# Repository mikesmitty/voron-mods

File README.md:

View this project on [CADLAB.io](https://cadlab.io/project/28137). 

# voron-mods

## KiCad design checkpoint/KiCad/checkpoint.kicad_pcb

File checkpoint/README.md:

# Checkpoint CANBUS board
STM32 CAN bus board for Klipper, modeled to fit over the A stepper on a Voron 2.4R2

# Development
View this project on [CADLAB.io](https://cadlab.io/project/28137/main/files/checkpoint/KiCad).

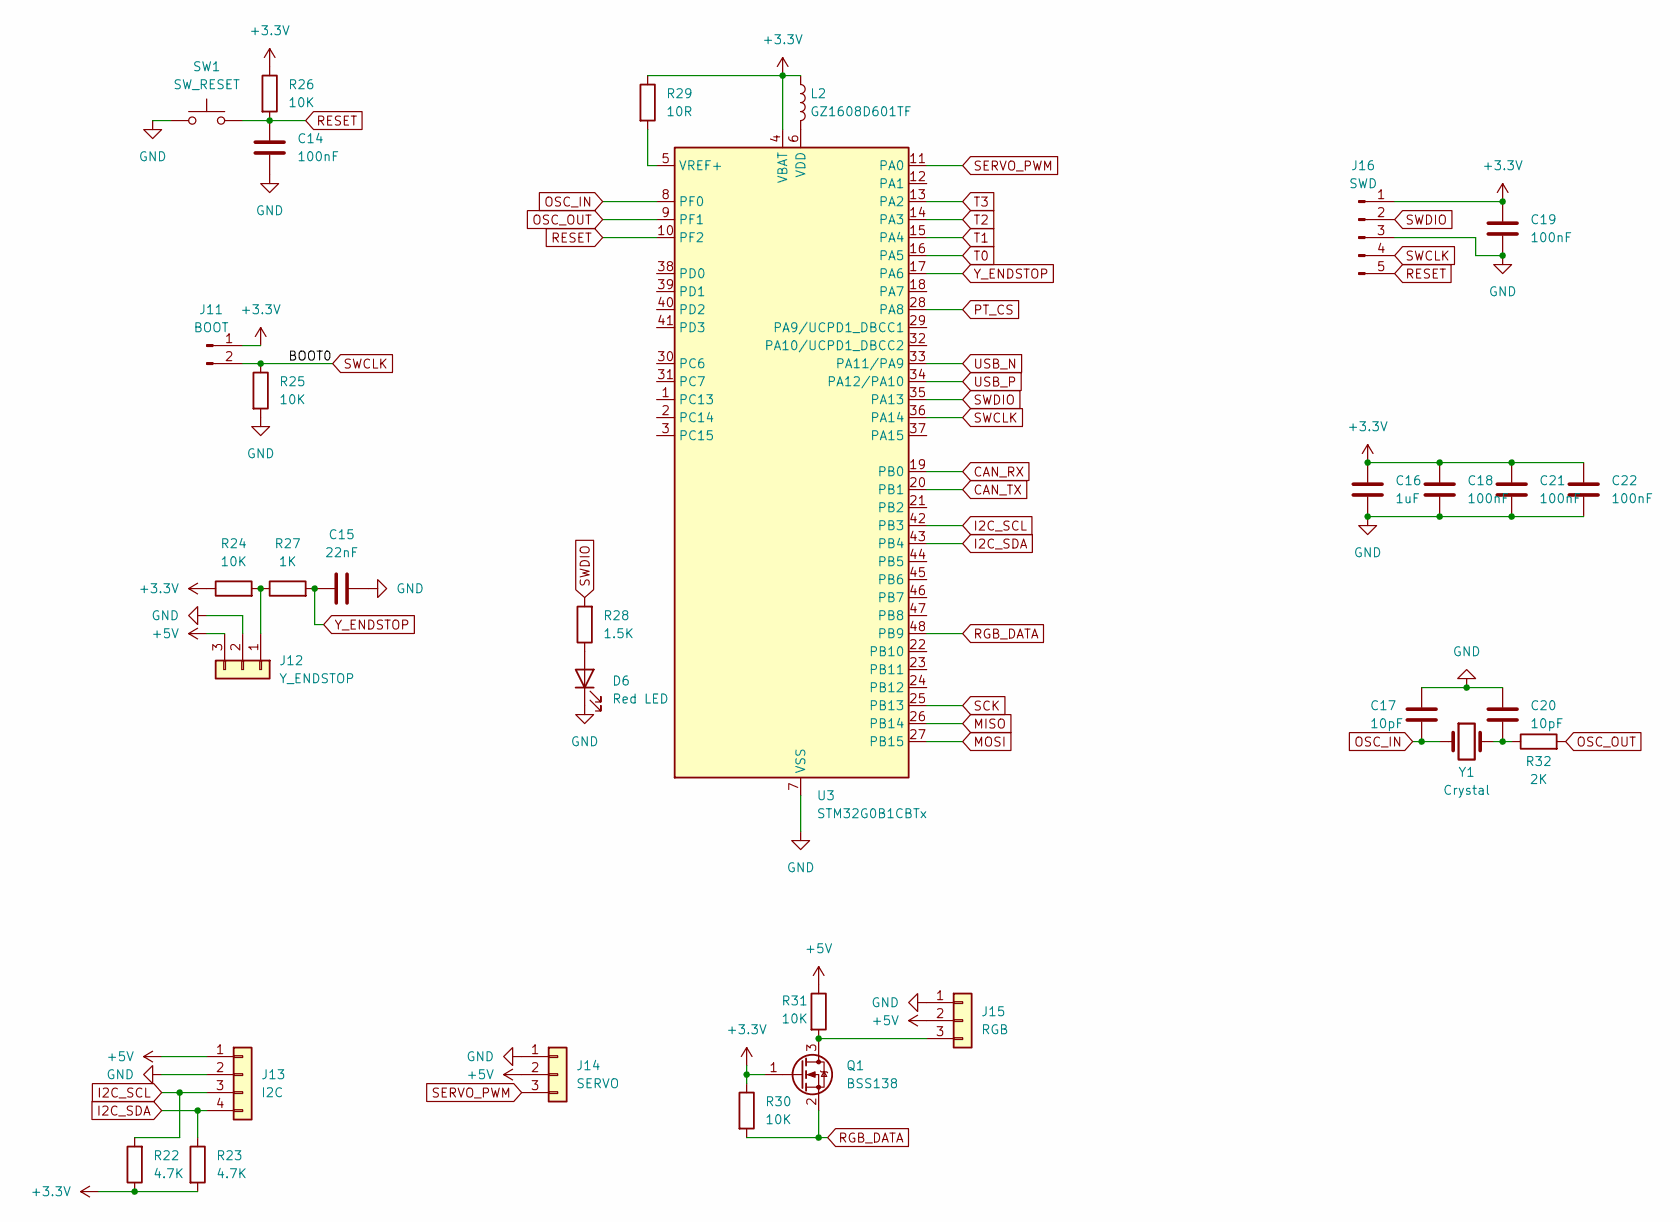
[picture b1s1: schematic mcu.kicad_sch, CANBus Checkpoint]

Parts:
C14, C18, C19, C21, C22: 100nF; C_0402_1005Metric
C15: 22nF; C_0603_1608Metric
C16: 1uF; C_0603_1608Metric
C17, C20: 10pF; C_0603_1608Metric
D6: Red LED; LED_0805_2012Metric
J11: BOOT; PinHeader_1x02_P2.54mm_Vertical
J12: Y_ENDSTOP; JST_XH_S3B-XH-A_1x03_P2.50mm_Horizontal
J13: I2C; JST_XH_B4B-XH-A_1x04_P2.50mm_Vertical
J14: SERVO; JST_XH_B3B-XH-A_1x03_P2.50mm_Vertical
J15: RGB; JST_XH_B3B-XH-A_1x03_P2.50mm_Vertical
J16: SWD; PinHeader_1x05_P2.54mm_Vertical
L2: GZ1608D601TF; L_0603_1608Metric
Q1: BSS138; SOT-23
R22, R23: 4.7K; R_0603_1608Metric
R24, R25, R26, R30, R31: 10K; R_0603_1608Metric
R27: 1K; R_0603_1608Metric
R28: 1.5K; R_0603_1608Metric
R29: 10R; R_0603_1608Metric
R32: 2K; R_0603_1608Metric
SW1: SW_RESET; SW_Push_1P1T_XKB_TS-1187A
U3: STM32G0B1CBTx; LQFP-48_7x7mm_P0.5mm
Y1: Crystal; Crystal_SMD_5032-2Pin_5.0x3.2mm

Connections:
+3.3V: C16.1, C18.1, C19.1, C21.1, C22.1, J11.1, J16.1, L2.1, Q1.1 (G), R22.1, R23.2, R24.1, R26.1, R29.1, R30.1, U3.4 (VBAT); also elsewhere on the board
+5V: J12.3, J13.1, J14.2, J15.2, R31.1; also elsewhere on the board
CAN_RX: U3.19 (PB0); also elsewhere on the board
CAN_TX: U3.20 (PB1); also elsewhere on the board
GND: C14.2, C15.2, C16.2, C17.2, C18.2, C19.2, C20.1, C21.2, C22.2, D6.1 (K), J12.2, J13.2, J14.1, J15.1, J16.3, R25.2, SW1.1, U3.7 (VSS); also elsewhere on the board
I2C_SCL: J13.3, R22.2, U3.42 (PB3)
I2C_SDA: J13.4, R23.1, U3.43 (PB4)
MISO: U3.26 (PB14); also elsewhere on the board
MOSI: U3.27 (PB15); also elsewhere on the board
unnamed: C20.2, R32.1, Y1.2
unnamed: D6.2 (A), R28.1
unnamed: J12.1, R24.2, R27.1
unnamed: J15.3, Q1.3 (D), R31.2
unnamed: L2.2, U3.6 (VDD)
unnamed: R29.2, U3.5 (VREF+)
OSC_IN: C17.1, U3.8 (PF0), Y1.1
OSC_OUT: R32.2, U3.9 (PF1)
PT_CS: U3.28 (PA8); also elsewhere on the board
RESET: C14.1, J16.5, R26.2, SW1.2, U3.10 (PF2)
RGB_DATA: Q1.2 (S), R30.2, U3.48 (PB9)
SCK: U3.25 (PB13); also elsewhere on the board
SERVO_PWM: J14.3, U3.11 (PA0)
SWCLK: J11.2, J16.4, R25.1, U3.36 (PA14)
SWDIO: J16.2, R28.2, U3.35 (PA13)
T0: U3.16 (PA5); also elsewhere on the board
T1: U3.15 (PA4); also elsewhere on the board
T2: U3.14 (PA3); also elsewhere on the board
T3: U3.13 (PA2); also elsewhere on the board
USB_N: U3.33 (PA11/PA9); also elsewhere on the board
USB_P: U3.34 (PA12/PA10); also elsewhere on the board
Y_ENDSTOP: C15.1, R27.2, U3.17 (PA6)

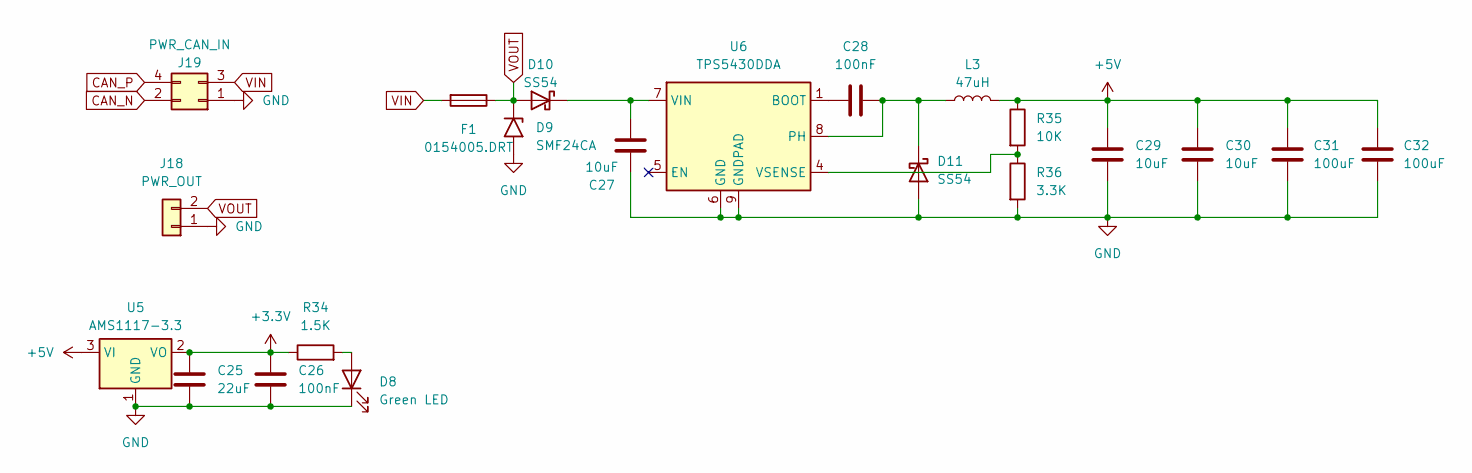
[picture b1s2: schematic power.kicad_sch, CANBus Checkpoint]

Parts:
C25: 22uF; C_0805_2012Metric
C26, C28: 100nF; C_0402_1005Metric
C27, C29, C30: 10uF; C_0805_2012Metric
C31, C32: 100uF; C_1206_3216Metric
D8: Green LED; LED_0805_2012Metric
D9: SMF24CA; D_SOD-123F
D10, D11: SS54; D_SMA
F1: 0154005.DRT; Fuseholder_Littelfuse_Nano2_154x
J18: PWR_OUT; TerminalBlock_Phoenix_MKDS-1,5-2-5.08_1x02_P5.08mm_Horizont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
J19: PWR_CAN_IN; Molex_Micro-Fit_3.0_43045-0412_2x02_P3.00mm_Vertical
L3: 47uH; L_Bourns_SRP7050WA_7.9x7.3mm
R34: 1.5K; R_0603_1608Metric
R35: 10K; R_0603_1608Metric
R36: 3.3K; R_0603_1608Metric
U5: AMS1117-3.3; SOT-223-3_TabPin2
U6: TPS5430DDA; TI_SO-PowerPAD-8_ThermalVias

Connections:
+3.3V: C25.1, C26.1, R34.1, U5.2 (VO); also elsewhere on the board
+5V: C29.1, C30.1, C31.1, C32.1, L3.2, R35.1, U5.3 (VI); also elsewhere on the board
CAN_N: J19.2; also elsewhere on the board
CAN_P: J19.4; also elsewhere on the board
GND: C25.2, C26.2, C27.2, C29.2, C30.2, C31.2, C32.2, D8.1 (K), D9.2 (A2), D11.2 (A), J18.1, J19.1, R36.2, U5.1 (GND), U6.6 (GND), U6.9 (GNDPAD); also elsewhere on the board
unnamed: D8.2 (A), R34.2
unnamed: C27.1, D10.1 (K), U6.7 (VIN)
unnamed: C28.2, D11.1 (K), L3.1, U6.8 (PH)
unnamed: C28.1, U6.1 (BOOT)
unnamed: R35.2, R36.1, U6.4 (VSENSE)
VIN: F1.2, J19.3
VOUT: D9.1 (A1), D10.2 (A), F1.1, J18.2

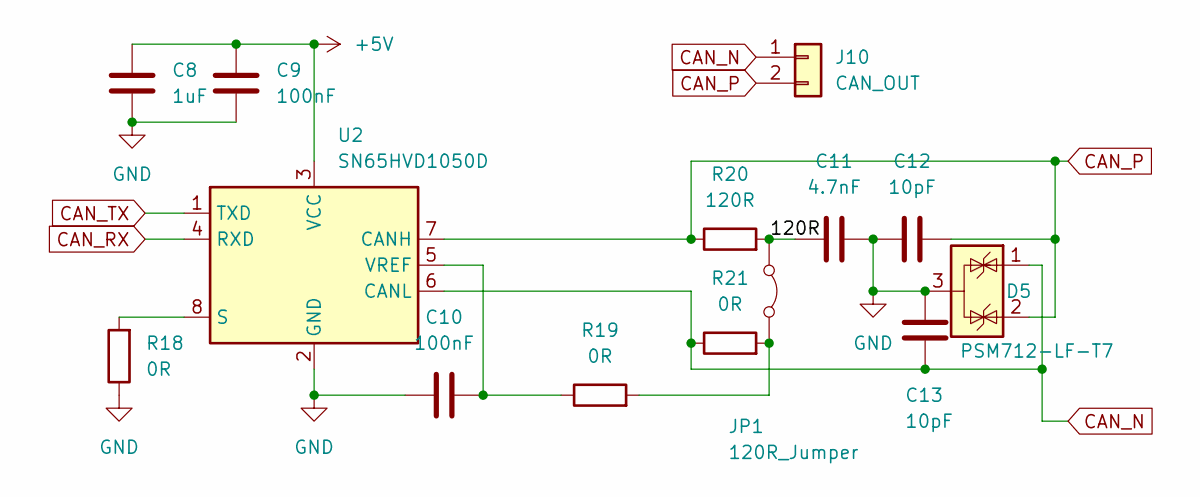
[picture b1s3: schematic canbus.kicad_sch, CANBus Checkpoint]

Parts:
C8: 1uF; C_0603_1608Metric
C9, C10: 100nF; C_0402_1005Metric
C11: 4.7nF; C_0603_1608Metric
C12, C13: 10pF; C_0603_1608Metric
D5: PSM712-LF-T7; SOT-23
J10: CAN_OUT; JST_XH_B2B-XH-A_1x02_P2.50mm_Vertical
JP1: 120R_Jumper; PinHeader_1x02_P2.54mm_Vertical
R18, R19, R21: 0R; R_0603_1608Metric
R20: 120R; R_0603_1608Metric
U2: SN65HVD1050D; SOIC-8_3.9x4.9mm_P1.27mm

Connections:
+5V: C8.2, C9.2, U2.3 (VCC); also elsewhere on the board
/CANBUS/120R: C11.1, JP1.1 (A), R20.2
CAN_N: C13.1, D5.1 (K), J10.1, R21.1, U2.6 (CANL); also elsewhere on the board
CAN_P: C12.2, D5.2 (K), J10.2, R20.1, U2.7 (CANH); also elsewhere on the board
CAN_RX: U2.4 (RXD); also elsewhere on the board
CAN_TX: U2.1 (TXD); also elsewhere on the board
GND: C8.1, C9.1, C10.1, C11.2, C12.1, C13.2, D5.3 (A), R18.1, U2.2 (GND); also elsewhere on the board
unnamed: JP1.2 (B), R19.2, R21.2
unnamed: R18.2, U2.8 (S)
unnamed: C10.2, R19.1, U2.5 (VREF)

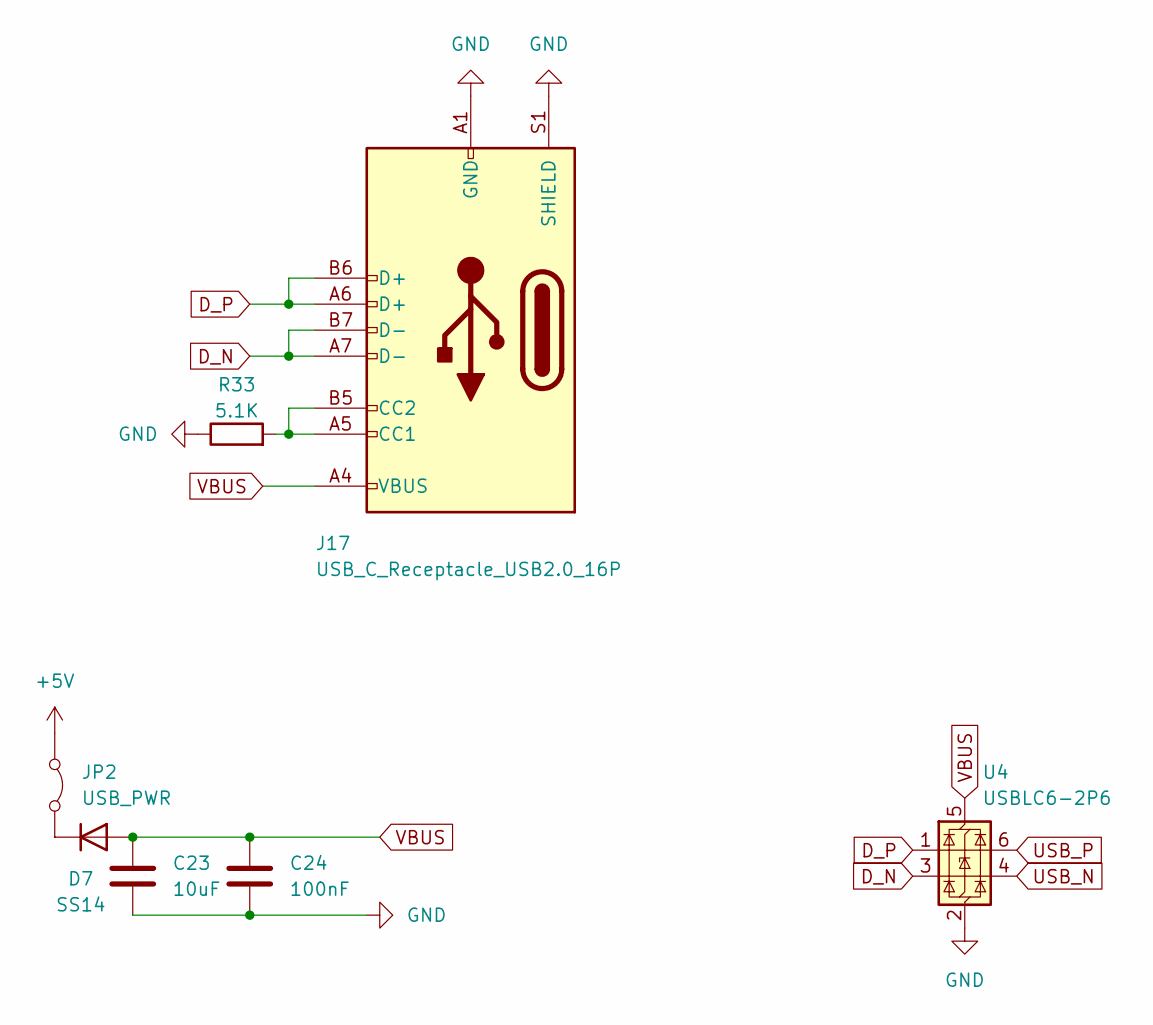
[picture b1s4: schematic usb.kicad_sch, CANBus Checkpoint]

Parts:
C23: 10uF; C_0805_2012Metric
C24: 100nF; C_0402_1005Metric
D7: SS14; D_SMA
J17: USB_C_Receptacle_USB2.0_16P; USB_C_14P_VERT_XUNPU
JP2: USB_PWR; PinHeader_1x02_P2.54mm_Vertical
R33: 5.1K; R_0603_1608Metric
U4: USBLC6-2P6; SOT-666

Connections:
+5V: JP2.1 (A); also elsewhere on the board
D_N: J17.A7 (D-), J17.B7 (D-), U4.3 (I/O2)
D_P: J17.A6 (D+), J17.B6 (D+), U4.1 (I/O1)
GND: C23.2, C24.2, J17.A1 (GND), J17.A12 (GND), J17.B1 (GND), J17.B12 (GND), J17.S1 (SHIELD), R33.1, U4.2 (GND); also elsewhere on the board
unnamed: D7.1 (K), JP2.2 (B)
unnamed: J17.A5 (CC1), J17.B5 (CC2), R33.2
USB_N: U4.4 (I/O2); also elsewhere on the board
USB_P: U4.6 (I/O1); also elsewhere on the board
VBUS: C23.1, C24.1, D7.2 (A), J17.A4 (VBUS), J17.A9 (VBUS), J17.B4 (VBUS), J17.B9 (VBUS), U4.5 (VBUS)

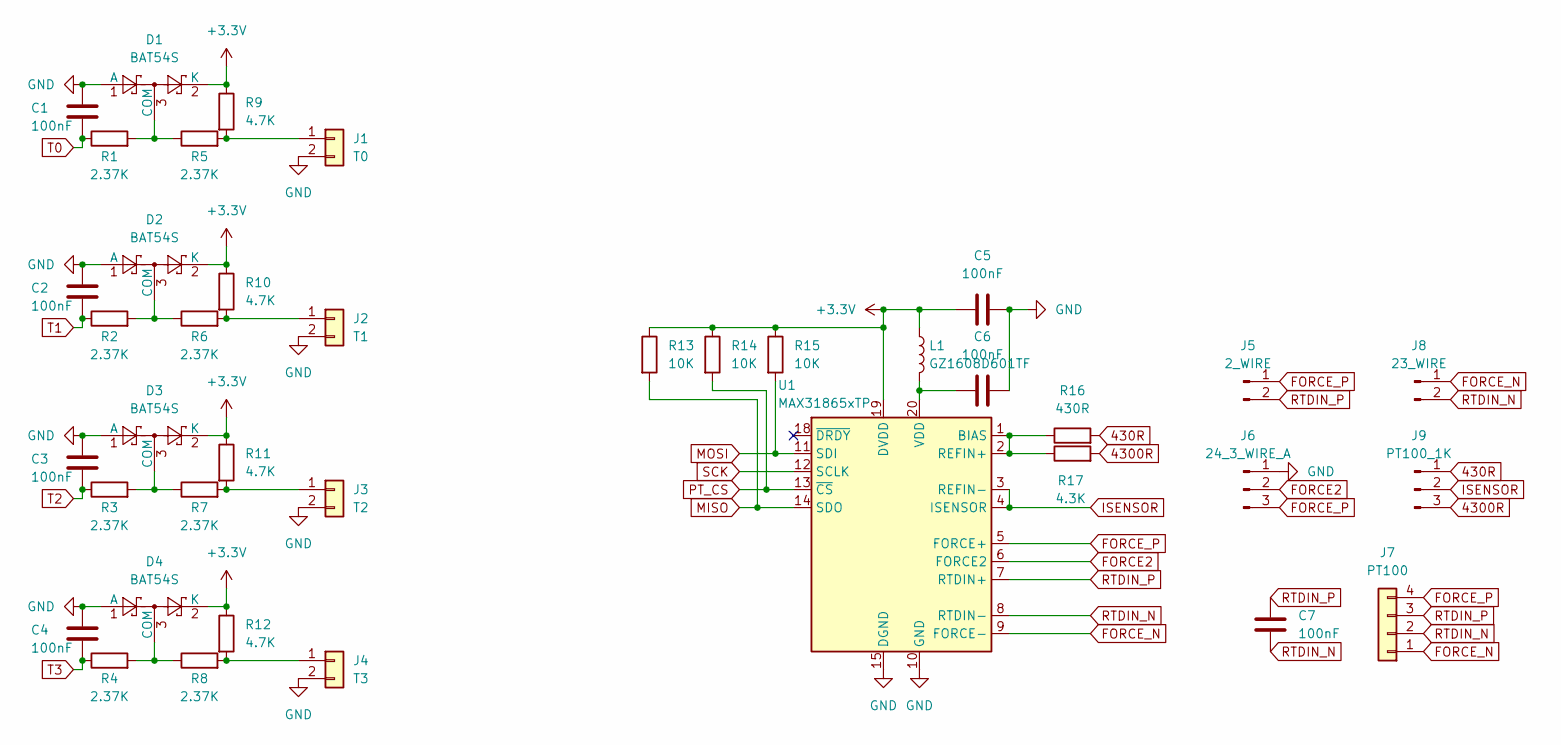
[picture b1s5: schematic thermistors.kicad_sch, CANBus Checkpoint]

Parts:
C1, C2, C3, C4, C5, C6, C7: 100nF; C_0402_1005Metric
D1, D2, D3, D4: BAT54S; SOT-23
J1: T0; JST_XH_B2B-XH-A_1x02_P2.50mm_Vertical
J2: T1; JST_XH_B2B-XH-A_1x02_P2.50mm_Vertical
J3: T2; JST_XH_B2B-XH-A_1x02_P2.50mm_Vertical
J4: T3; JST_XH_B2B-XH-A_1x02_P2.50mm_Vertical
J5: 2_WIRE; PinHeader_1x02_P2.54mm_Vertical
J6: 24_3_WIRE_A; PinHeader_1x03_P2.54mm_Vertical
J7: PT100; JST_XH_B4B-XH-A_1x04_P2.50mm_Vertical
J8: 23_WIRE; PinHeader_1x02_P2.54mm_Vertical
J9: PT100_1K; PinHeader_1x03_P2.54mm_Vertical
L1: GZ1608D601TF; L_0603_1608Metric
R1, R2, R3, R4, R5, R6, R7, R8: 2.37K; R_0603_1608Metric
R9, R10, R11, R12: 4.7K; R_0603_1608Metric
R13, R14, R15: 10K; R_0603_1608Metric
R16: 430R; R_0603_1608Metric
R17: 4.3K; R_0603_1608Metric
U1: MAX31865xTP; TQFN-20-1EP_5x5mm_P0.65mm_EP3.25x3.25mm

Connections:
430R: J9.1, R16.2
4300R: J9.3, R17.2
+3.3V: C5.1, D1.2 (K), D2.2 (K), D3.2 (K), D4.2 (K), L1.1, R9.1, R10.1, R11.1, R12.1, R13.1, R14.1, R15.1, U1.19 (DVDD); also elsewhere on the board
FORCE2: J6.2, U1.6 (FORCE2)
FORCE_N: J7.1, J8.1, U1.9 (FORCE-)
FORCE_P: J5.1, J6.3, J7.4, U1.5 (FORCE+)
GND: C1.2, C2.2, C3.2, C4.2, C5.2, C6.2, D1.1 (A), D2.1 (A), D3.1 (A), D4.1 (A), J1.2, J2.2, J3.2, J4.2, J6.1, U1.10 (GND), U1.15 (DGND), U1.16 (GND), U1.21 (GND); also elsewhere on the board
ISENSOR: J9.2, U1.3 (REFIN-), U1.4 (ISENSOR)
MISO: R13.2, U1.14 (SDO); also elsewhere on the board
MOSI: R15.2, U1.11 (SDI); also elsewhere on the board
unnamed: D1.3 (COM), R1.2, R5.1
unnamed: D2.3 (COM), R2.2, R6.1
unnamed: D3.3 (COM), R3.2, R7.1
unnamed: D4.3 (COM), R4.2, R8.1
unnamed: J1.1, R5.2, R9.2
unnamed: J2.1, R6.2, R10.2
unnamed: J3.1, R7.2, R11.2
unnamed: J4.1, R8.2, R12.2
unnamed: R16.1, R17.1, U1.1 (BIAS), U1.2 (REFIN+)
unnamed: C6.1, L1.2, U1.20 (VDD)
PT_CS: R14.2, U1.13 (~CS); also elsewhere on the board
RTDIN_N: C7.2, J7.2, J8.2, U1.8 (RTDIN-)
RTDIN_P: C7.1, J5.2, J7.3, U1.7 (RTDIN+)
SCK: U1.12 (SCLK); also elsewhere on the board
T0: C1.1, R1.1; also elsewhere on the board
T1: C2.1, R2.1; also elsewhere on the board
T2: C3.1, R3.1; also elsewhere on the board
T3: C4.1, R4.1; also elsewhere on the board

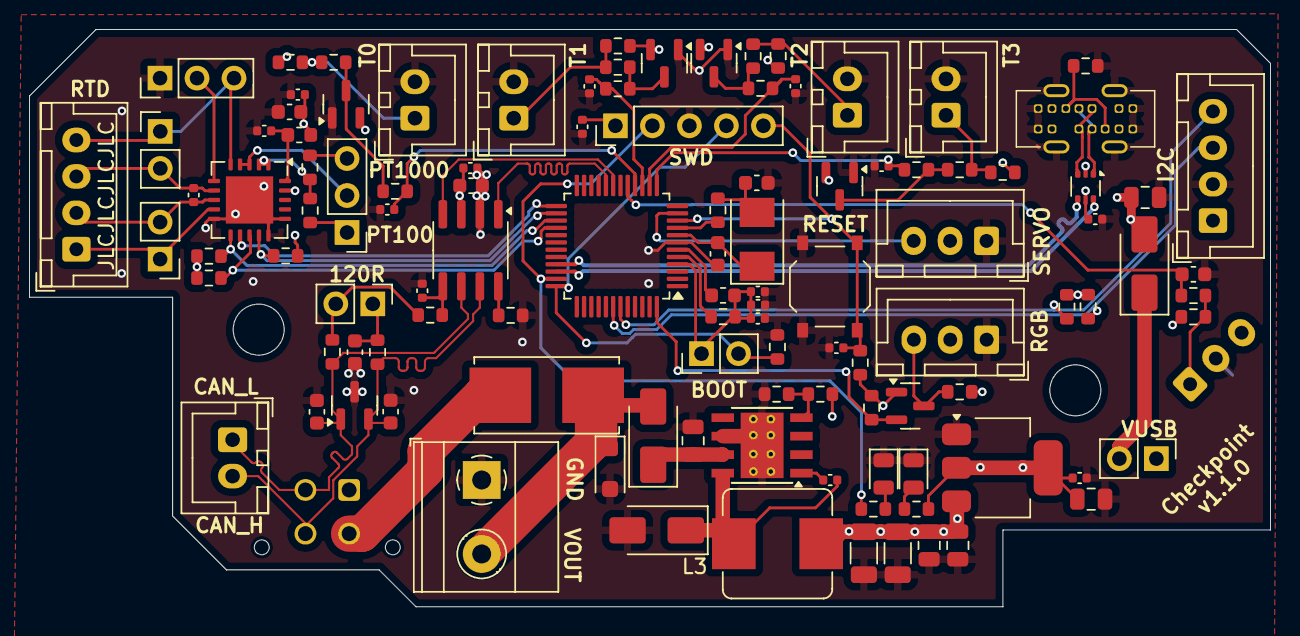
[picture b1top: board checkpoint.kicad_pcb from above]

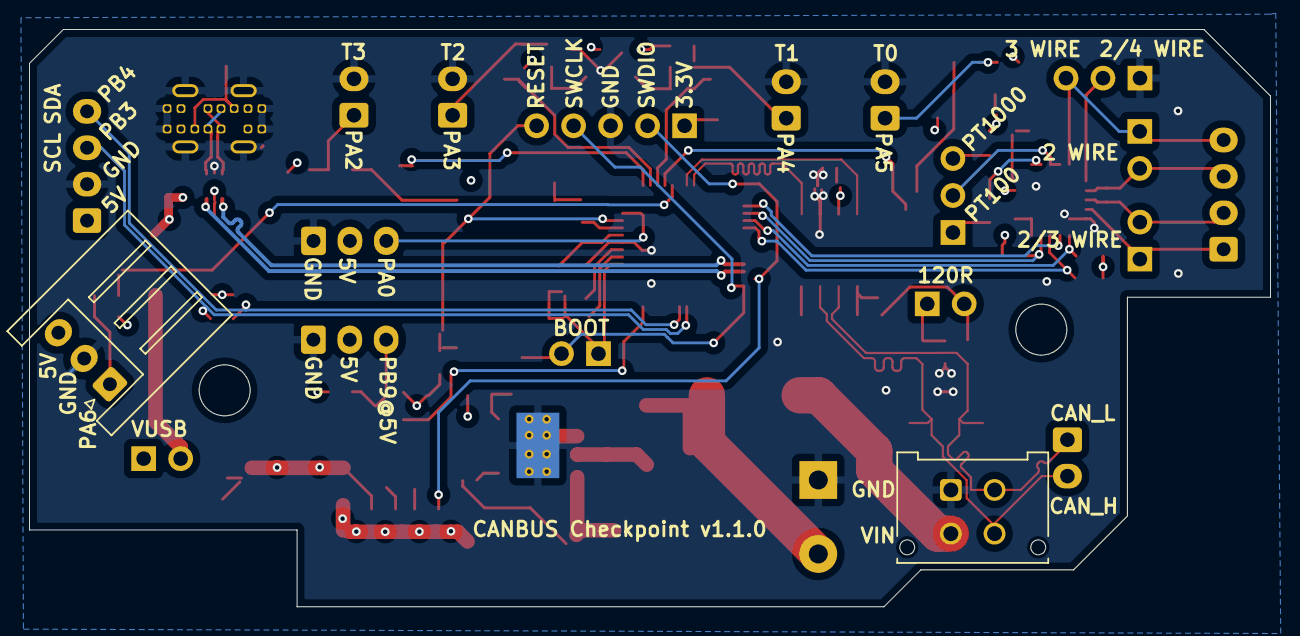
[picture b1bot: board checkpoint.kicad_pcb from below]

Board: 4 copper layers, 85.2 x 39.6 mm, 113 parts (2 on the bottom side), 67 nets.

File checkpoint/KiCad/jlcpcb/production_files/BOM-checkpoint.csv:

Comment,Designator,Footprint,LCSC
GZ1608D601TF,"L1,L2",L_0603_1608Metric,C1002
Crystal,Y1,Crystal_SMD_5032-2Pin_5.0x3.2mm,C115962
MAX31865xTP,U1,TQFN-20-1EP_5x5mm_P0.65mm_EP3.25x3.25mm,C118474
SN65HVD1050D,U2,SOIC-8_3.9x4.9mm_P1.27mm,C14019
100uF,"C31,C32",C_1206_3216Metric,C15008
100nF,"C1,C10,C14,C18,C19,C2,C21,C22,C24,C26,C28,C3,C4,C5,C6,C7,C9",C_0402_1005Metric,C1525
1uF,"C16,C8",C_0603_1608Metric,C15849
10uF,"C23,C27,C29,C30",C_0805_2012Metric,C15850
USBLC6-2P6,U4,SOT-666,C15999
10pF,"C12,C13,C17,C20",C_0603_1608Metric,C1634
SMF24CA,D9,D_SOD-123F,C19077515
0154005.DRT,F1,Fuseholder_Littelfuse_Nano2_154x,C206917
22nF,C15,C_0603_1608Metric,C21122
0R,"R18,R19,R21",R_0603_1608Metric,C21189
1K,R27,R_0603_1608Metric,C21190
SS54,"D10,D11",D_SMA,C22452
120R,R20,R_0603_1608Metric,C22787
1.5K,"R28,R34",R_0603_1608Metric,C22843
10R,R29,R_0603_1608Metric,C22859
Green LED,D8,LED_0805_2012Metric,C2297
2K,R32,R_0603_1608Metric,C22975
3.3K,R36,R_0603_1608Metric,C22978
4.3K,R17,R_0603_1608Metric,C23159
4.7K,"R10,R11,R12,R22,R23,R9",R_0603_1608Metric,C23162
430R,R16,R_0603_1608Metric,C23170
5.1K,R33,R_0603_1608Metric,C23186
SS14,D7,D_SMA,C2480
10K,"R13,R14,R15,R24,R25,R26,R30,R31,R35",R_0603_1608Metric,C25804
2.37K,"R1,R2,R3,R4,R5,R6,R7,R8",R_0603_1608Metric,C25964
STM32G0B1CBTx,U3,LQFP-48_7x7mm_P0.5mm,C2847904
USB_C_Receptacle_USB2.0_16P,J17,USB_C_14P_VERT_XUNPU,C2982529
SW_RESET,SW1,SW_Push_1P1T_XKB_TS-1187A,C318884
PSM712-LF-T7,D5,SOT-23,C32677
22uF,C25,C_0805_2012Metric,C45783
4.7nF,C11,C_0603_1608Metric,C53987
AMS1117-3.3,U5,SOT-223-3_TabPin2,C6186
BAT54S,"D1,D2,D3,D4",SOT-23,C7420333
BSS138,Q1,SOT-23,C7420339
Red LED,D6,LED_0805_2012Metric,C84256
TPS5430DDA,U6,TI_SO-PowerPAD-8_ThermalVias,C9864
T0,J1,JST_XH_B2B-XH-A_1x02_P2.50mm_Vertical,
120R_Jumper,JP1,PinHeader_1x02_P2.54mm_Vertical,
T1,J2,JST_XH_B2B-XH-A_1x02_P2.50mm_Vertical,
CAN_OUT,J10,JST_XH_B2B-XH-A_1x02_P2.50mm_Vertical,
PWR_OUT,J18,"TerminalBlock_Phoenix_MKDS-1,5-2-5.08_1x02_P5.08mm_Horizontal",
USB_PWR,JP2,PinHeader_1x02_P2.54mm_Vertical,
23_WIRE,J8,PinHeader_1x02_P2.54mm_Vertical,
RGB,J15,JST_XH_B3B-XH-A_1x03_P2.50mm_Vertical,
SWD,J16,PinHeader_1x05_P2.54mm_Vertical,
24_3_WIRE_A,J6,PinHeader_1x03_P2.54mm_Vertical,
T2,J3,JST_XH_B2B-XH-A_1x02_P2.50mm_Vertical,
2_WIRE,J5,PinHeader_1x02_P2.54mm_Vertical,
47uH,L3,L_Bourns_SRP7050WA_7.9x7.3mm,
BOOT,J11,PinHeader_1x02_P2.54mm_Vertical,
SERVO,J14,JST_XH_B3B-XH-A_1x03_P2.50mm_Vertical,
PT100,J7,JST_XH_B4B-XH-A_1x04_P2.50mm_Vertical,
I2C,J13,JST_XH_B4B-XH-A_1x04_P2.50mm_Vertical,
PT100_1K,J9,PinHeader_1x03_P2.54mm_Vertical,
T3,J4,JST_XH_B2B-XH-A_1x02_P2.50mm_Vertical,
PWR_CAN_IN,J19,Molex_Micro-Fit_3.0_43045-0412_2x02_P3.00mm_Vertical,
Y_ENDSTOP,J12,JST_XH_S3B-XH-A_1x03_P2.50mm_Horizontal,

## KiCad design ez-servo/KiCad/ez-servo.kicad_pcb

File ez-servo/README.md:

# EZ Servo - High Voltage Servo Driver
Turn an unused EZ stepper driver socket on your BTT MMB into a high voltage (6.0V/8.4V) servo output for running high voltage servos with higher torque.

### DC-DC voltage converter board for use with EZ stepper driver sockets on the BTT MMB control board
 - TPS5430DDA Step-down converter configured for 6.0V or 8.4V output, up to 3A
 - Pin header with servo output
 - Optionally, use stepper motor output on controller board as servo output (1B: GND, 2B: VCC, 1A: SIG)

Parts that need to be sourced if assembled by JLC:
  - 1-2x 3-Pin Headers [Right Angle Header 2.54mm Pitch](https://www.digikey.com/en/products/detail/molex/0022286030/3158667) or similar 
  - Output Inductor 47uH [Bourns SRP7050WA-470M](https://www.digikey.com/en/products/detail/bourns-inc/srp7050wa-470m/18670339)

```
[servo ez_servo]
# Uncomment the pin for the socket used
#pin: mmb:PB15 # EZ Driver1
#pin: mmb:PD2  # EZ Driver2
#pin: mmb:PD0  # EZ Driver3
#pin: mmb:PB6  # EZ Driver4
```

# Development
View this project on [CADLAB.io](https://cadlab.io/project/28137/main/files/ez-servo/KiCad).

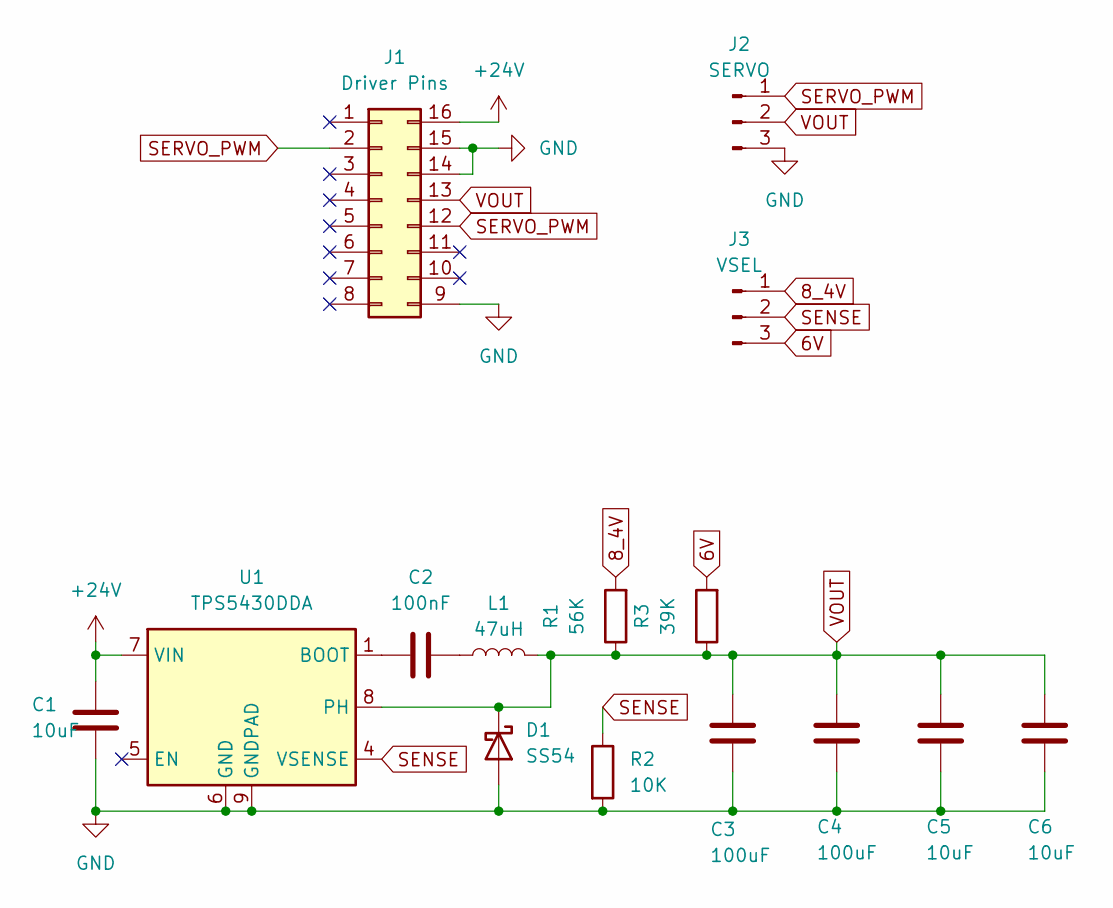
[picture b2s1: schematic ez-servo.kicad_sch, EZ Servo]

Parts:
C1, C5, C6: 10uF; C_0805_2012Metric
C2: 100nF; C_0805_2012Metric
C3, C4: 100uF; C_1206_3216Metric
D1: SS54; D_SMA
J1: Driver Pins; BTT EZ
J2: SERVO; PinHeader_1x03_P2.54mm_Vertical
J3: VSEL; PinHeader_1x03_P2.54mm_Horizontal
L1: 47uH; L_Bourns_SRP7050WA_7.9x7.3mm
R1: 56K; R_0805_2012Metric_Pad1.20x1.40mm_HandSolder
R2: 10K; R_0805_2012Metric_Pad1.20x1.40mm_HandSolder
R3: 39K; R_0805_2012Metric_Pad1.20x1.40mm_HandSolder
U1: TPS5430DDA; TI_SO-PowerPAD-8_ThermalVias

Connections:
6V: J3.3, R3.2
8_4V: J3.1, R1.2
+24V: C1.1, J1.16, U1.7 (VIN)
GND: C1.2, C3.2, C4.2, C5.2, C6.2, D1.2 (A), J1.9, J1.14, J1.15, J2.3, R2.2, U1.6 (GND), U1.9 (GNDPAD)
unnamed: C2.2, L1.1
unnamed: C2.1, U1.1 (BOOT)
SENSE: J3.2, R2.1, U1.4 (VSENSE)
SERVO_PWM: J1.2, J1.12, J2.1
VOUT: C3.1, C4.1, C5.1, C6.1, D1.1 (K), J1.13, J2.2, L1.2, R1.1, R3.1, U1.8 (PH)

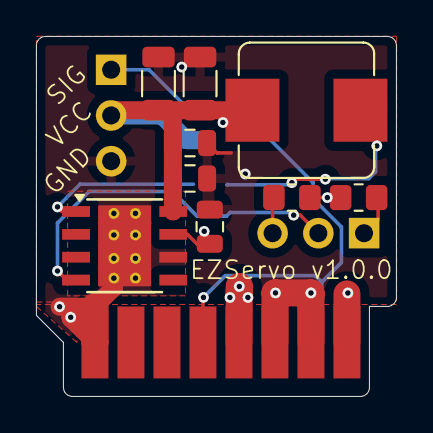
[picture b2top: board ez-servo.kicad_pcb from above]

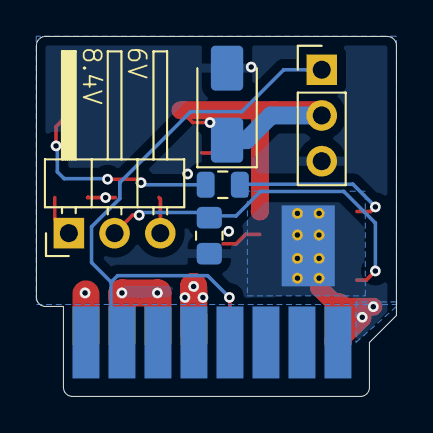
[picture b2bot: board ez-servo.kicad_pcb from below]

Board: 4 copper layers, 20.0 x 20.0 mm, 15 parts (6 on the bottom side), 9 nets.

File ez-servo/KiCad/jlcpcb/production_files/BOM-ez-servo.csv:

Comment,Designator,Footprint,LCSC
100uF,"C3,C4",C_1206_3216Metric,C15008
10uF,"C1,C5,C6",C_0805_2012Metric,C15850
10K,R2,R_0805_2012Metric_Pad1.20x1.40mm_HandSolder,C17414
SS54,D1,D_SMA,C22452
39K,R3,R_0805_2012Metric_Pad1.20x1.40mm_HandSolder,C23153
56K,R1,R_0805_2012Metric_Pad1.20x1.40mm_HandSolder,C23206
100nF,C2,C_0805_2012Metric,C28233
TPS5430DDA,U1,TI_SO-PowerPAD-8_ThermalVias,C9864

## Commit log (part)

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2024-05-21 chore: initial commit of pcb v1.1
2024-05-21 Backlink to CADLAB.io has been added.
2024-05-22 chore: remove 3.3v trace overlapping 3.3v zone
2024-05-22 chore: add pcb lock files to .gitignore
2024-05-22 chore: make some space between fused vin/vout traces
    chore: cleanup traces
2024-05-22 chore: traces cleanup
2024-05-24 chore: clear space around mount holes
2024-05-25 fix: rotate backwards filter diode
2024-05-25 chore: update .gitignore for kicad lock files
2024-05-25 chore: reset refdes numbers
2024-05-25 fix: add i2c pullup resistors
2024-05-26 fix: swap can lines to match BTT convention
2024-05-26 chore: switch to vertical usb-c port
2024-05-26 chore: add hidden jlcpcb order number token
2024-05-27 feat: add initial STLs
2024-05-27 chore: move pcb step file to CAD folder
2024-05-27 fix: thicken endstop mount section
2024-05-27 chore: remove reference designators and clean up silkscreen
2024-05-27 feat: add inductor to support 3A@5V output
2024-05-27 chore: update component rotation
2024-05-27 chore: update component bom excludes
2024-05-27 chore: rename checkpoint pcb folder
2024-05-28 chore: add release-please and test kibot
2024-05-28 chore(deps): add renovate.json
2024-05-28 chore(main): release 1.0.0
2024-05-28 chore: test release-please output
2024-05-28 chore: update release-please manifest
2024-05-28 chore(main): release 1.1.0
2024-05-28 chore: update dates in KiCad files on push
2024-05-28 chore: update revisions with release-please tagged version
2024-05-28 chore: move kicad revision updates to separate workflow
2024-05-28 chore: fix paren escaping
2024-05-28 chore: only update revisions if changelog updated
2024-05-28 chore: make revision update more flexible
2024-05-28 chore: fix paren escaping again
2024-05-28 chore: allow committing to branch
2024-05-28 chore: don't run on individual push
2024-05-28 chore: avoid shallow clones
2024-05-28 chore: checkout branches
2024-05-28 chore: fix pcb export trigger
2024-05-28 chore: update path for kibot cad export
2024-05-28 chore: set working directory for kibot
2024-05-28 chore: try to set board path for kibot
2024-05-28 chore: locate pcb file
2024-05-28 chore: add output dir to kibot update
2024-05-28 chore: debug kibot output
2024-05-28 chore: convert absolute paths to relative
2024-05-28 chore: don't canonicalize the board path
2024-05-28 chore: fix relative path conversion
2024-05-28 chore: delete log files
2024-05-28 chore: clean up tracks
2024-05-28 chore: KiBot CAD update
2024-05-28 chore(deps): add renovate.json (#1)
2024-05-28 chore(deps): update inti-cmnb/kibot action to v2
2024-05-28 chore: simplify kibot outputs
2024-05-30 fix: fix thread pitch for cnlinko lp-12/m12 connector
2024-06-01 chore: re-save project file with DRC exclusions
2024-06-01 feat: initial ez-servo PCB
2024-06-01 fix: replace undersized protection diodes
2024-06-01 chore: update project file
2024-06-01 chore: fix release please syntax
2024-06-01 chore: split release PRs
2024-06-01 chore: update release-please reference
2024-06-01 fix: add silkscreen markings
2024-06-01 chore: add kibot cad output config
2024-06-01 fix: switch feedback resistor footprints for flexibility
2024-06-01 feat: add optional servo output through stepper port
2024-06-01 chore: set origins
2024-06-01 fix: round off connector corners
2024-06-01 chore: add ez-servo readme
2024-06-01 chore: update readme files
2024-06-01 fix: move dimension info off edge.cuts layer
2024-06-01 fix: round off sharp corners
2024-06-01 chore: update KiCad revisions
2024-08-23 chore(deps): update tj-actions/changed-files action to v45
2024-08-24 chore(deps): update tj-actions/changed-files action to v45 (#22)
2024-09-25 chore(deps): update ghcr.io/inti-cmnb/kicad8_auto docker tag to v1.8.1
2024-09-26 chore(deps): update ghcr.io/inti-cmnb/kicad8_auto docker tag to v1.8.1 (#23)
2025-03-16 chore(deps): update tj-actions/changed-files action to v46
2025-03-16 chore(deps): update tj-actions/changed-files action to v46 (#25)
2025-03-18 chore(deps): update ghcr.io/inti-cmnb/kicad8_auto docker tag to v1.8.3
2025-03-24 chore(deps): update ghcr.io/inti-cmnb/kicad8_auto docker tag to v1.8.3 (#24)
2025-04-03 chore(deps): update ghcr.io/inti-cmnb/kicad8_auto docker tag to v1.8.4
2025-04-05 chore(deps): update ghcr.io/inti-cmnb/kicad8_auto docker tag to v1.8.4 (#26)
2025-08-11 chore(deps): update actions/checkout action to v5
2025-08-12 chore(deps): update actions/checkout action to v5 (#27)
2025-09-13 chore(deps): update tj-actions/changed-files action to v47
2025-09-18 chore(deps): update tj-actions/changed-files action to v47 (#28)
2025-11-23 chore: Update actions/checkout action to v6
2025-11-23 chore: Update actions/checkout action to v6 (#29)
2025-12-15 chore: Update INTI-CMNB/KiBot action to v2
2025-12-17 chore: Update ghcr.io/inti-cmnb/kicad8_auto Docker tag to v1.8.5
2026-04-23 chore: Update googleapis/release-please-action action to v5
2026-04-25 chore: Update EndBug/add-and-commit action to v10
2026-06-19 chore: Update actions/checkout action to v7

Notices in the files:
checkpoint/KiCad/canbus.kicad_sch:
creativecommons.org/licenses/by-sa/4.0
License: CC BY-SA 4.0
